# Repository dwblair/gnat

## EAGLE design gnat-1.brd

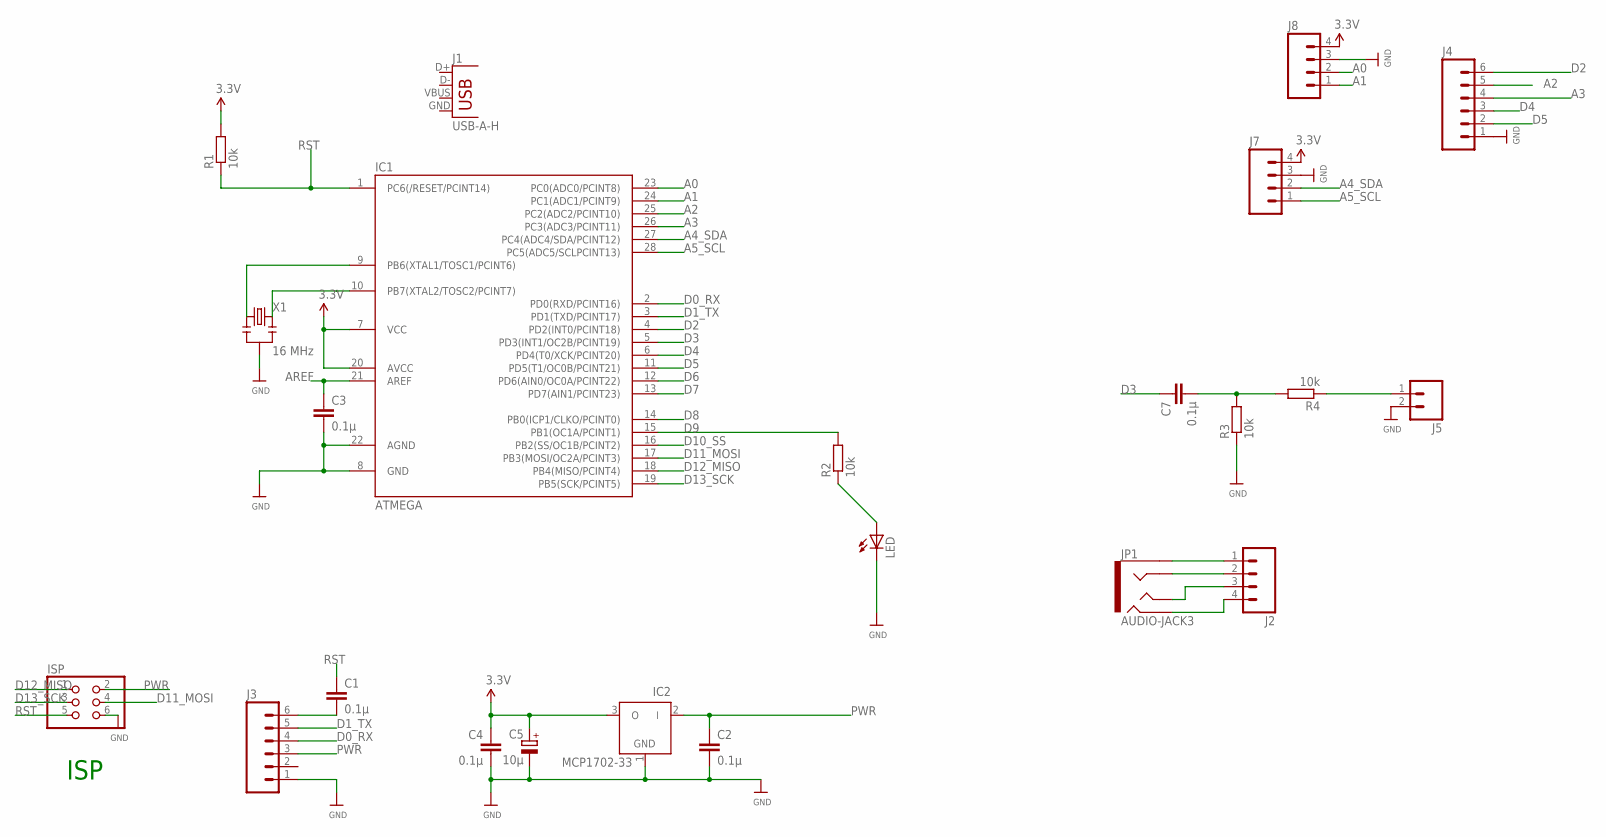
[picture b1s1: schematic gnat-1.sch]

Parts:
C1, C2, C3, C4, C7: 0.1µ; C025-024X044
C5: 10µ; E1,8-4
IC1: ATMEGA; DIL28-3
IC2: MCP1702-33; TO92
ISP: PINHD-2X3; 2X03
J1: USB-A-H
J2: M04PTH; 1X04
J3, J4: M06SILK_FEMALE_PTH; 1X06
J5: M02PTH; 1X02
J7, J8: M04SCREW; SCREWTERMINAL-3.5MM-4
JP1: AUDIO-JACK3; AUDIO-JACK-TRRS-SMD
LED: LED3MM
R1, R2, R3, R4: 10k; 0204/7
X1: 16 MHz; RESONATOR-PTH

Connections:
A0: IC1.23 (PC0(ADC0/PCINT8)), J8.2
A1: IC1.24 (PC1(ADC1/PCINT9)), J8.1
A2: IC1.25 (PC2(ADC2/PCINT10)), J4.5
A3: IC1.26 (PC3(ADC3/PCINT11)), J4.4
A4_SDA: IC1.27 (PC4(ADC4/SDA/PCINT12)), J7.2
A5_SCL: IC1.28 (PC5(ADC5/SCLPCINT13)), J7.1
AREF: C3.1, IC1.21 (AREF)
D0_RX: IC1.2 (PD0(RXD/PCINT16)), J3.4
D1_TX: IC1.3 (PD1(TXD/PCINT17)), J3.5
D2: IC1.4 (PD2(INT0/PCINT18)), J4.6
D3: C7.1, IC1.5 (PD3(INT1/OC2B/PCINT19))
D4: IC1.6 (PD4(T0/XCK/PCINT20)), J4.3
D5: IC1.11 (PD5(T1/OC0B/PCINT21)), J4.2
D6: IC1.12 (PD6(AIN0/OC0A/PCINT22))
D7: IC1.13 (PD7(AIN1/PCINT23))
D8: IC1.14 (PB0(ICP1/CLKO/PCINT0))
D9: IC1.15 (PB1(OC1A/PCINT1)), R2.2
D10_SS: IC1.16 (PB2(SS/OC1B/PCINT2))
D11_MOSI: IC1.17 (PB3(MOSI/OC2A/PCINT3)), ISP.4
D12_MISO: IC1.18 (PB4(MISO/PCINT4)), ISP.1
D13_SCK: IC1.19 (PB5(SCK/PCINT5)), ISP.3
GND: C2.2, C3.2, C4.2, C5.-, IC1.8 (GND), IC1.22 (AGND), IC2.1 (GND), ISP.6, J3.1, J4.1, J5.2, J7.3, J8.3, LED.K (C), R3.1, X1.2
unnamed: IC1.9 (PB6(XTAL1/TOSC1/PCINT6)), X1.1
unnamed: LED.A, R2.1
unnamed: J2.1, JP1.EARTH
unnamed: J2.2, JP1.RING1
unnamed: J2.3, JP1.TIP
unnamed: J2.4, JP1.RING2
unnamed: C7.2, R3.2, R4.2
unnamed: J5.1, R4.1
unnamed: C1.2, J3.6
unnamed: IC1.10 (PB7(XTAL2/TOSC2/PCINT7)), X1.3
PWR: C2.1, IC2.2 (I), ISP.2, J3.3
RST: C1.1, IC1.1 (PC6(/RESET/PCINT14)), ISP.5, R1.1
VCC: C4.1, C5.+, IC1.7 (VCC), IC1.20 (AVCC), IC2.3 (O), J7.4, J8.4, R1.2

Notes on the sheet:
ISP

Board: 2 copper layers, 23 parts (0 on the bottom side), 31 nets, no tracks yet.

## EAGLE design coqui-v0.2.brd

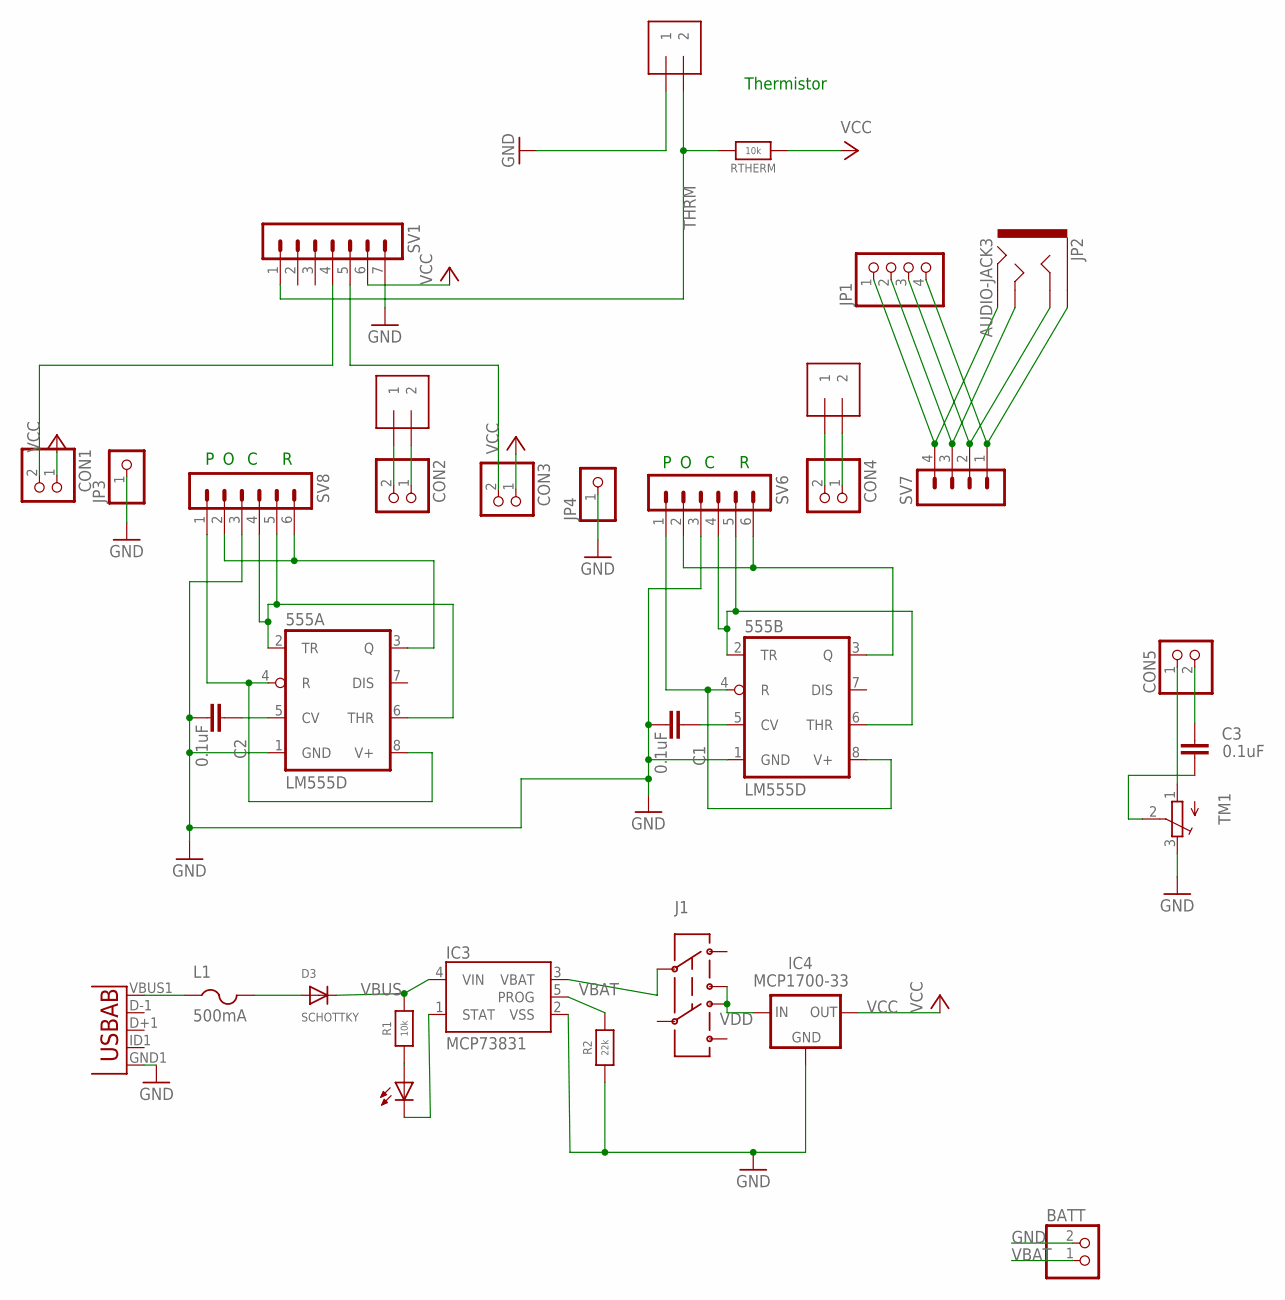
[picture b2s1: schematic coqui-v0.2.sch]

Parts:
555A, 555B: LM555D; SO08
BATT: JST_2PIN-SMT-RA; JST-PH-2-SMT-RA
C1, C2, C3: 0.1uF; 0603-CAP
CHG: 0805; CHIPLED_0805
CON1, CON2, CON3, CON4, CON5: PINHD-1X2; 1X02
D3: SCHOTTKY; SOD-123FL
IC3: MCP73831; SOT23-5
IC4: MCP1700-33; SOT89
IN1, IN2: 1X2-3.5MM
J1: AYZ0202
JP1: PINHD-1X4/90; 1X04/90
JP2: AUDIO-JACK3; AUDIO-JACK-TRRS-SMD
JP3, JP4: PINHD-1X1; 1X01
L1: 500mA; R1206
R1: 10k; 0603-NO
R2: 22k; 0603-NO
RTHERM: 10k; 0603-NO
SV1: MA07-1
SV6, SV8: MA06-1
SV7: MA04-1
THRM: 1X2-3.5MM
TM1: TRIMPOTTC33X; TC33X
U$4: USB-AB""; USB-AB-MICRO-SMD_V02_BOSS

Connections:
AOUT: 555A.3 (Q), SV8.2, SV8.6
AOUT1: 555B.3 (Q), SV6.2, SV6.6
GND: 555A.1 (GND), 555B.1 (GND), BATT.2 (1), C1.1, C2.1, IC3.2 (VSS), IC4.1 (GND), JP3.1, JP4.1, R2.1, SV1.7, SV6.3, SV8.3, THRM.1, TM1.3 (E), U$4.GND1 (GND)
unnamed: 555B.2 (TR), 555B.6 (THR), SV6.4, SV6.5
unnamed: 555B.5 (CV), C1.2
unnamed: IC3.5 (PROG), R2.2
unnamed: CHG.A, R1.1
unnamed: CHG.C, IC3.1 (STAT)
unnamed: JP1.4, JP2.EARTH, SV7.1
unnamed: JP1.3, JP2.RING1, SV7.2
unnamed: JP1.2, JP2.TIP, SV7.3
unnamed: JP1.1, JP2.RING2, SV7.4
unnamed: CON2.2, IN1.1
unnamed: 555A.2 (TR), 555A.6 (THR), SV8.4, SV8.5
unnamed: L1.1, U$4.VBUS1 (VBUS)
unnamed: D3.A, L1.2
unnamed: 555A.5 (CV), C2.2
unnamed: CON2.1, IN1.2
unnamed: CON4.2, IN2.1
unnamed: CON4.1, IN2.2
unnamed: CON1.2, SV1.4
unnamed: CON3.2, SV1.5
unnamed: CON5.1, TM1.1 (A)
unnamed: C3.2, CON5.2
unnamed: C3.1, TM1.2 (S)
THRM: RTHERM.2, SV1.1, THRM.2
VAIN: 555A.4 (R), 555A.8 (V+), SV8.1
VAIN1: 555B.4 (R), 555B.8 (V+), SV6.1
VBAT: BATT.1 (2), IC3.3 (VBAT), J1.2
VBUS: D3.C, IC3.4 (VIN), R1.2
VCC: CON1.1, CON3.1, IC4.3 (OUT), RTHERM.1, SV1.6
VDD: IC4.2 (IN), J1.1 (3), J1.6 (4)

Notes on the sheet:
Thermistor

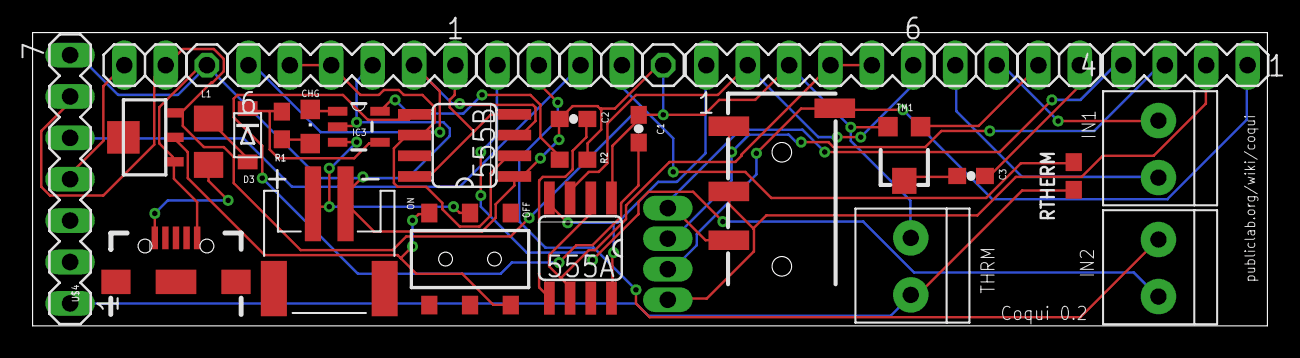
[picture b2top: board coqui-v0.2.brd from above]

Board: 2 copper layers, 75.8 x 18.0 mm, 33 parts (0 on the bottom side), 32 nets.

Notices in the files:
parts and their libraries:
SparkFun-Connectors: Licensing: Creative Commons ShareAlike 4.0 International - https://creativecommons.org/licenses/by-sa/4.0
microbuilder: This work is placed in the public domain, and may be freely used for commercial and non-commercial work with the following conditions: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
